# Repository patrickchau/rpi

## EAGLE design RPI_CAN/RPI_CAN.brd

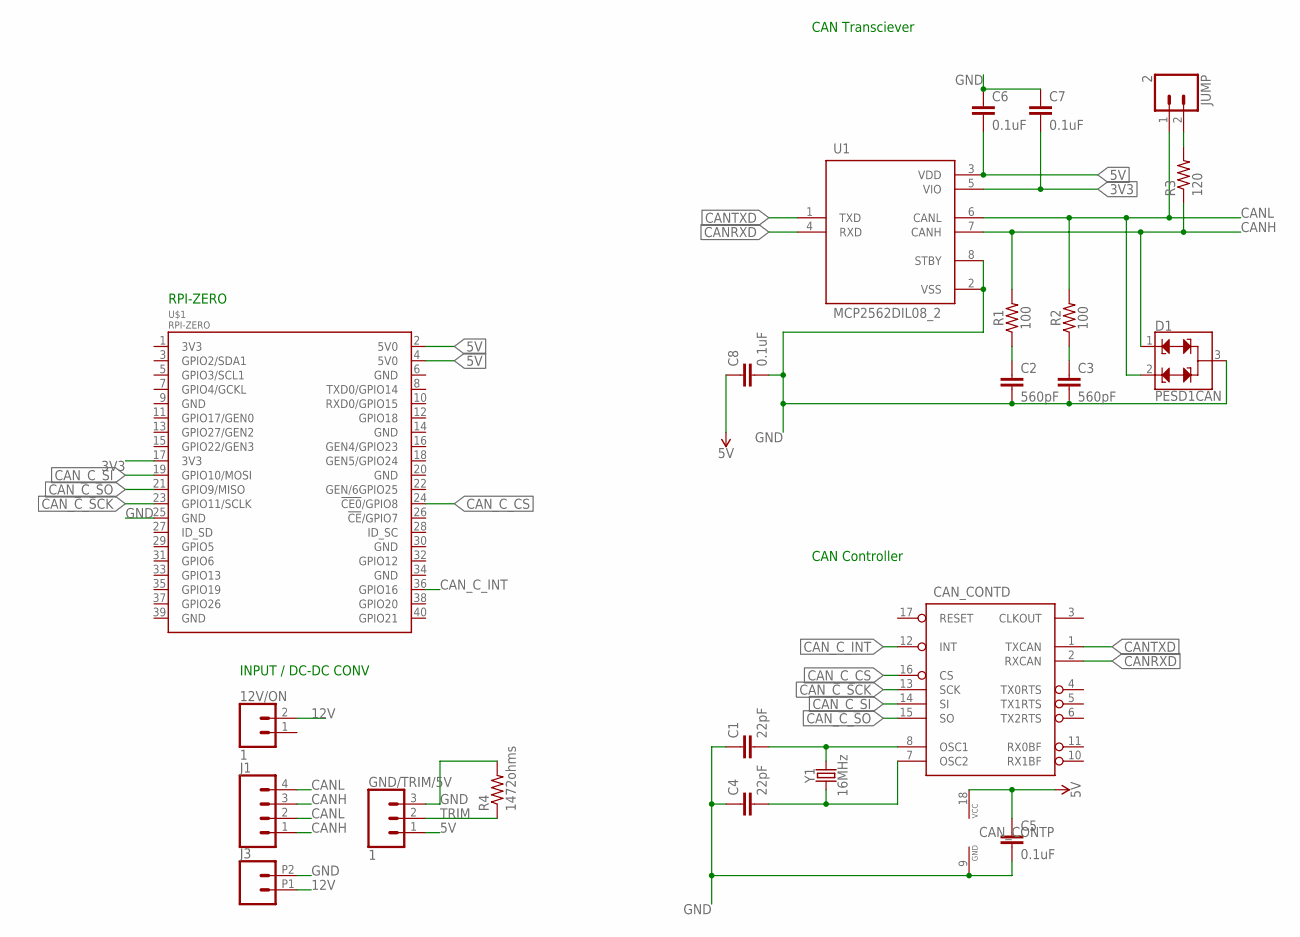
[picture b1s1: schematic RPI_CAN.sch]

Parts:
12V/ON: 1; 1X02
C1, C4: 22pF; CAP-PTH-SMALL-KIT
C2, C3: 560pF; CAP-PTH-SMALL-KIT
C5, C6, C7, C8: 0.1uF; CAP-PTH-SMALL-KIT
CAN_CONT: MCP2515P; DIL18
D1: PESD1CAN; SOT23-3
GND/TRIM/5V: 1; 1X03
J1: CONN_04; 1X04
J3: CONN_022.54MM_SCREWTERM; 1X02_2.54_SCREWTERM
JUMP: 2; 1X02
R1, R2: 100; AXIAL-0.3EZ
R3: 120; AXIAL-0.3
R4: 1472ohms; 0204/5
U1: MCP2562DIL08_2; DIL08
U$1: RPI-ZERO; RASP_PI_ZERO_BOARD_FULL
Y1: 16MHz; HC49US

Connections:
3V3: C7.2, U1.5 (VIO), U$1.17 (3V3)
5V: C5.1, C6.2, C8.1, CAN_CONT.18 (VCC), GND/TRIM/5V.1, U1.3 (VDD), U$1.2 (5V0), U$1.4 (5V0)
12V: 12V/ON.2, J3.P1 (1)
CANH: D1.1, J1.1, J1.3, R1.P$2 (2), R3.P$1 (1), U1.7 (CANH)
CANL: D1.2, J1.2, J1.4, JUMP.1, R2.P$2 (2), U1.6 (CANL)
CANRXD: CAN_CONT.2 (RXCAN), U1.4 (RXD)
CANTXD: CAN_CONT.1 (TXCAN), U1.1 (TXD)
CAN_C_CS: CAN_CONT.16 (CS), U$1.24 (!CE0!/GPIO8)
CAN_C_INT: CAN_CONT.12 (INT), U$1.36 (GPIO16)
CAN_C_SCK: CAN_CONT.13 (SCK), U$1.23 (GPIO11/SCLK)
CAN_C_SI: CAN_CONT.14 (SI), U$1.19 (GPIO10/MOSI)
CAN_C_SO: CAN_CONT.15 (SO), U$1.21 (GPIO9/MISO)
GND: C1.1, C2.2, C3.2, C4.1, C5.2, C6.1, C7.1, C8.2, CAN_CONT.9 (GND), D1.3, GND/TRIM/5V.3, J3.P2 (2), R4.2, U1.2 (VSS), U1.8 (STBY), U$1.25 (GND)
unnamed: JUMP.2, R3.P$2 (2)
unnamed: C2.1, R1.P$1 (1)
unnamed: C3.1, R2.P$1 (1)
unnamed: C1.2, CAN_CONT.8 (OSC1), Y1.2
unnamed: C4.2, CAN_CONT.7 (OSC2), Y1.1
TRIM: GND/TRIM/5V.2, R4.1

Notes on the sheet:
CAN Transciever
CAN Controller
INPUT / DC-DC CONV
RPI-ZERO

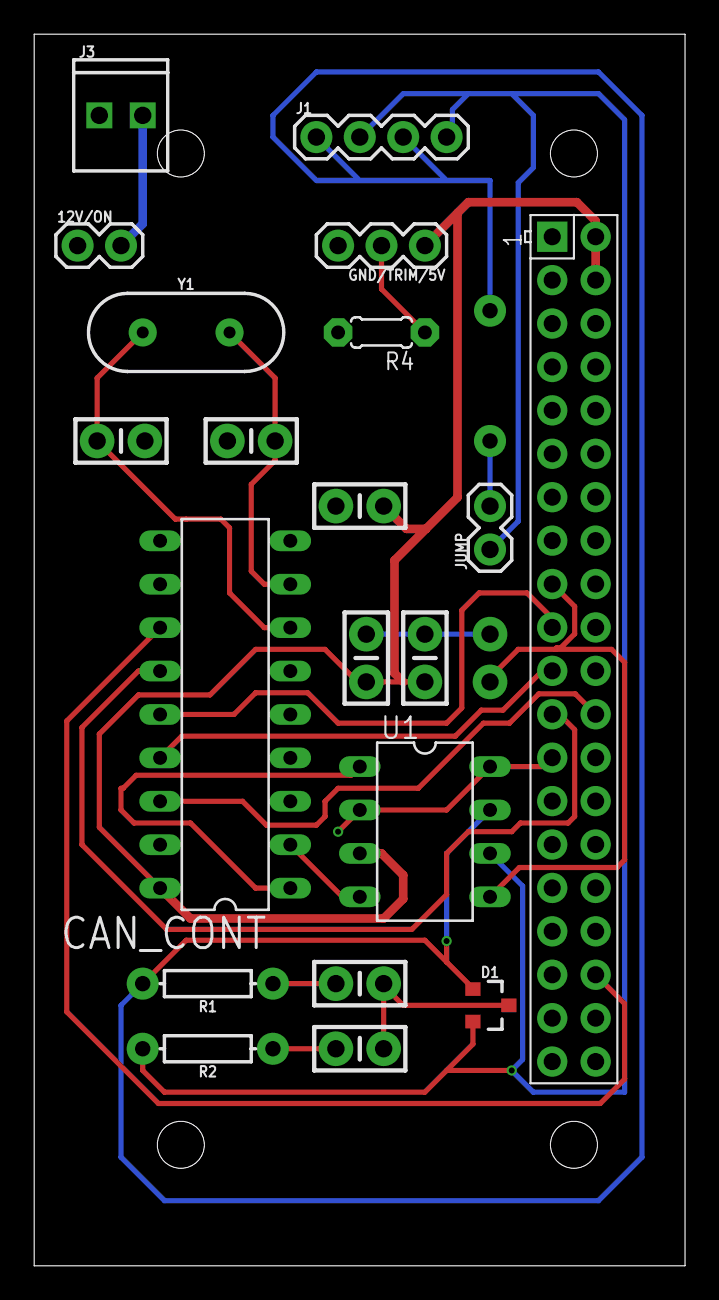
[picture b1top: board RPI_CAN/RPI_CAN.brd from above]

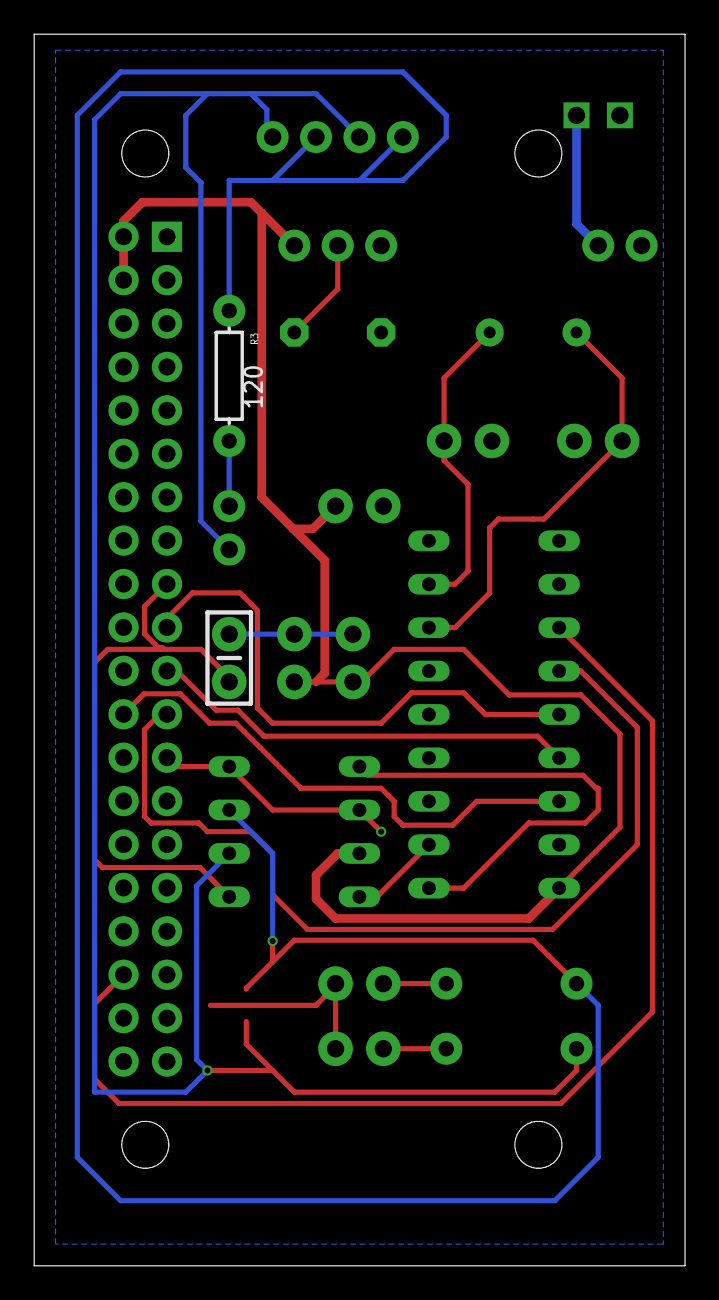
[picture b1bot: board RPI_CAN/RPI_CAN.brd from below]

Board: 2 copper layers, 38.1 x 72.1 mm, 22 parts (2 on the bottom side), 19 nets.

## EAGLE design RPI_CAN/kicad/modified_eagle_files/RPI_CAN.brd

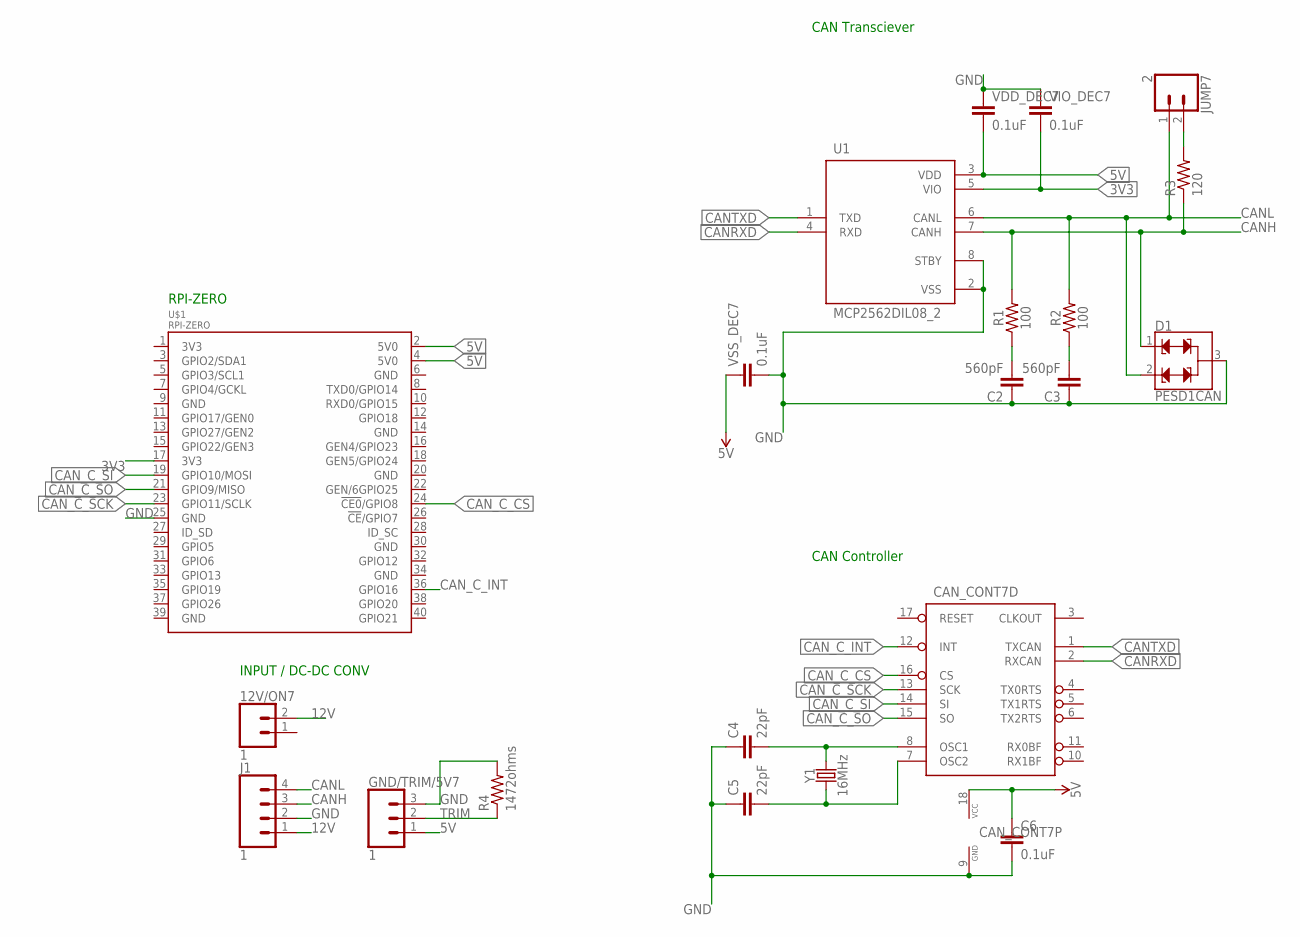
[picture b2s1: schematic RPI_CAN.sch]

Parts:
12V/ON7: 1; 1X02
C2, C3: 560pF; CAP-PTH-SMALL-KIT
C4, C5: 22pF; CAP-PTH-2.54
C6: 0.1uF; CAP-PTH-SMALL-KIT
CAN_CONT7: MCP2515P; DIL18
D1: PESD1CAN; SOT23-3
GND/TRIM/5V7: 1; 1X03
J1: 1; SCREWTERMINAL-3.5MM-4
JUMP7: 2; 1X02
R1, R2: 100; AXIAL-0.3EZ
R3: 120; AXIAL-0.3
R4: 1472ohms; 0204/5
U1: MCP2562DIL08_2; DIL08
U$1: RPI-ZERO; RASP_PI_ZERO_BOARD_FULL
VDD_DEC7: 0.1uF; CAP-PTH-SMALL-KIT
VIO_DEC7: 0.1uF; CAP-PTH-SMALL-KIT
VSS_DEC7: 0.1uF; CAP-PTH-SMALL-KIT
Y1: 16MHz; HC49US

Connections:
3V3: U1.5 (VIO), U$1.17 (3V3), VIO_DEC7.2
5V: C6.1, CAN_CONT7.18 (VCC), GND/TRIM/5V7.1, U1.3 (VDD), U$1.2 (5V0), U$1.4 (5V0), VDD_DEC7.2, VSS_DEC7.1
12V: 12V/ON7.2, J1.1
CANH: D1.1, J1.3, R1.P$2 (2), R3.P$1 (1), U1.7 (CANH)
CANL: D1.2, J1.4, JUMP7.1, R2.P$2 (2), U1.6 (CANL)
CANRXD: CAN_CONT7.2 (RXCAN), U1.4 (RXD)
CANTXD: CAN_CONT7.1 (TXCAN), U1.1 (TXD)
CAN_C_CS: CAN_CONT7.16 (CS), U$1.24 (!CE0!/GPIO8)
CAN_C_INT: CAN_CONT7.12 (INT), U$1.36 (GPIO16)
CAN_C_SCK: CAN_CONT7.13 (SCK), U$1.23 (GPIO11/SCLK)
CAN_C_SI: CAN_CONT7.14 (SI), U$1.19 (GPIO10/MOSI)
CAN_C_SO: CAN_CONT7.15 (SO), U$1.21 (GPIO9/MISO)
GND: C2.1, C3.1, C4.1, C5.1, C6.2, CAN_CONT7.9 (GND), D1.3, GND/TRIM/5V7.3, J1.2, R4.2, U1.2 (VSS), U1.8 (STBY), U$1.25 (GND), VDD_DEC7.1, VIO_DEC7.1, VSS_DEC7.2
unnamed: JUMP7.2, R3.P$2 (2)
unnamed: C2.2, R1.P$1 (1)
unnamed: C3.2, R2.P$1 (1)
unnamed: C4.2, CAN_CONT7.8 (OSC1), Y1.2
unnamed: C5.2, CAN_CONT7.7 (OSC2), Y1.1
TRIM: GND/TRIM/5V7.2, R4.1

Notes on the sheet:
CAN Transciever
CAN Controller
INPUT / DC-DC CONV
RPI-ZERO

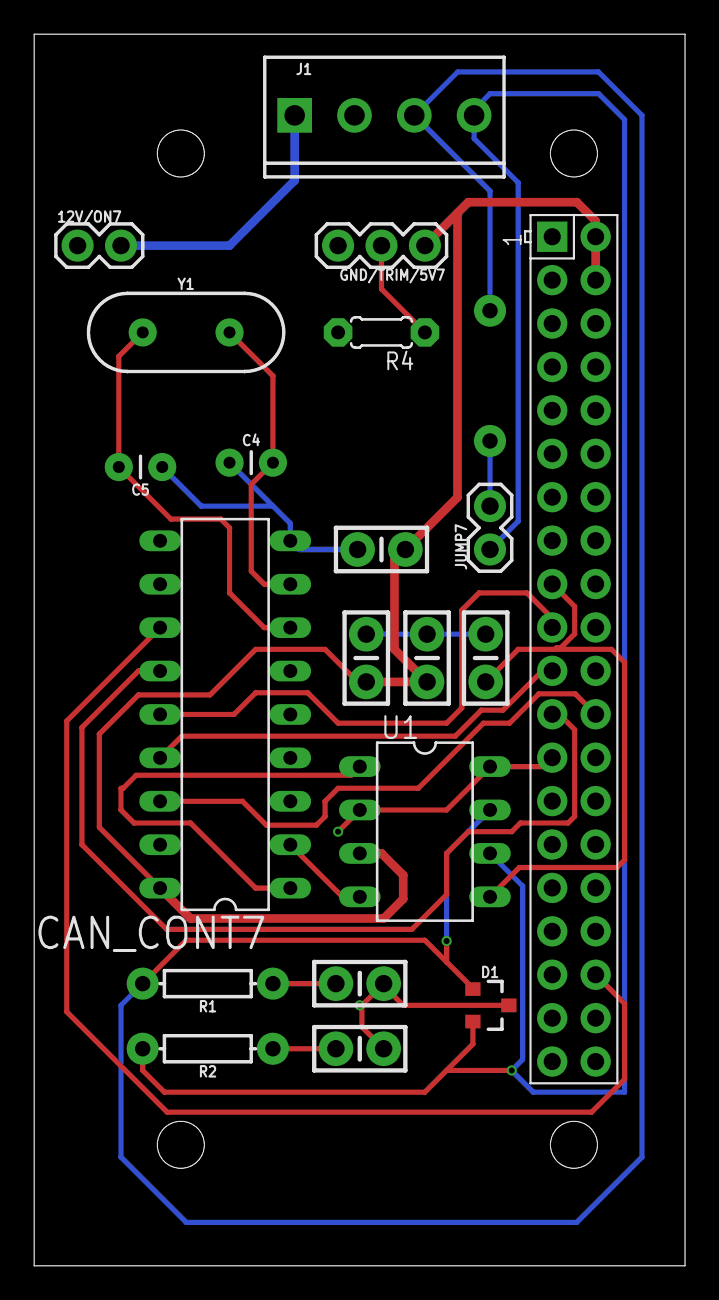
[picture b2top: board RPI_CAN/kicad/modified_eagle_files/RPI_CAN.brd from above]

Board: 2 copper layers, 38.1 x 72.1 mm, 21 parts (1 on the bottom side), 19 nets.

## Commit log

2020-06-28 initial upload
2020-06-28 added eagle files

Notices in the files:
parts and their libraries:
SparkFun-DiscreteSemi: Licensing: Creative Commons ShareAlike 4.0 International - https://creativecommons.org/licenses/by-sa/4.0
SparkFun: Licensing: CC v3.0 Share-Alike You are welcome to use this library for commercial purposes.
